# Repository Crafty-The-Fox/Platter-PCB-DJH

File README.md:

# Custom drop-in replacement for the DJ Hero plater PCB with Kailh Choc Mini Switch

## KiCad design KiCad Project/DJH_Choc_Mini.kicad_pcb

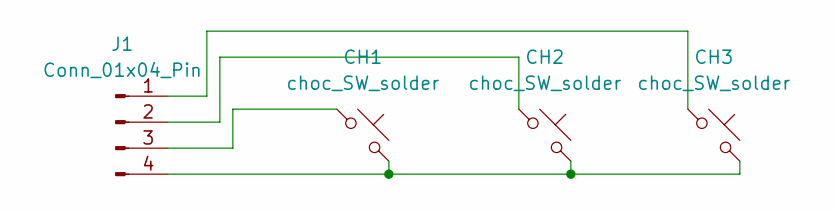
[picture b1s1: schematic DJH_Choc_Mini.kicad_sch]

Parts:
CH1, CH2, CH3: choc_SW_solder; SW_Kailh_Choc_Mini
J1: Conn_01x04_Pin; PinSocket_1x04_P2.54mm_Vertical

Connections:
unnamed: CH3.1, J1.1
unnamed: CH2.1, J1.2
unnamed: CH1.1, J1.3
unnamed: CH1.2, CH2.2, CH3.2, J1.4

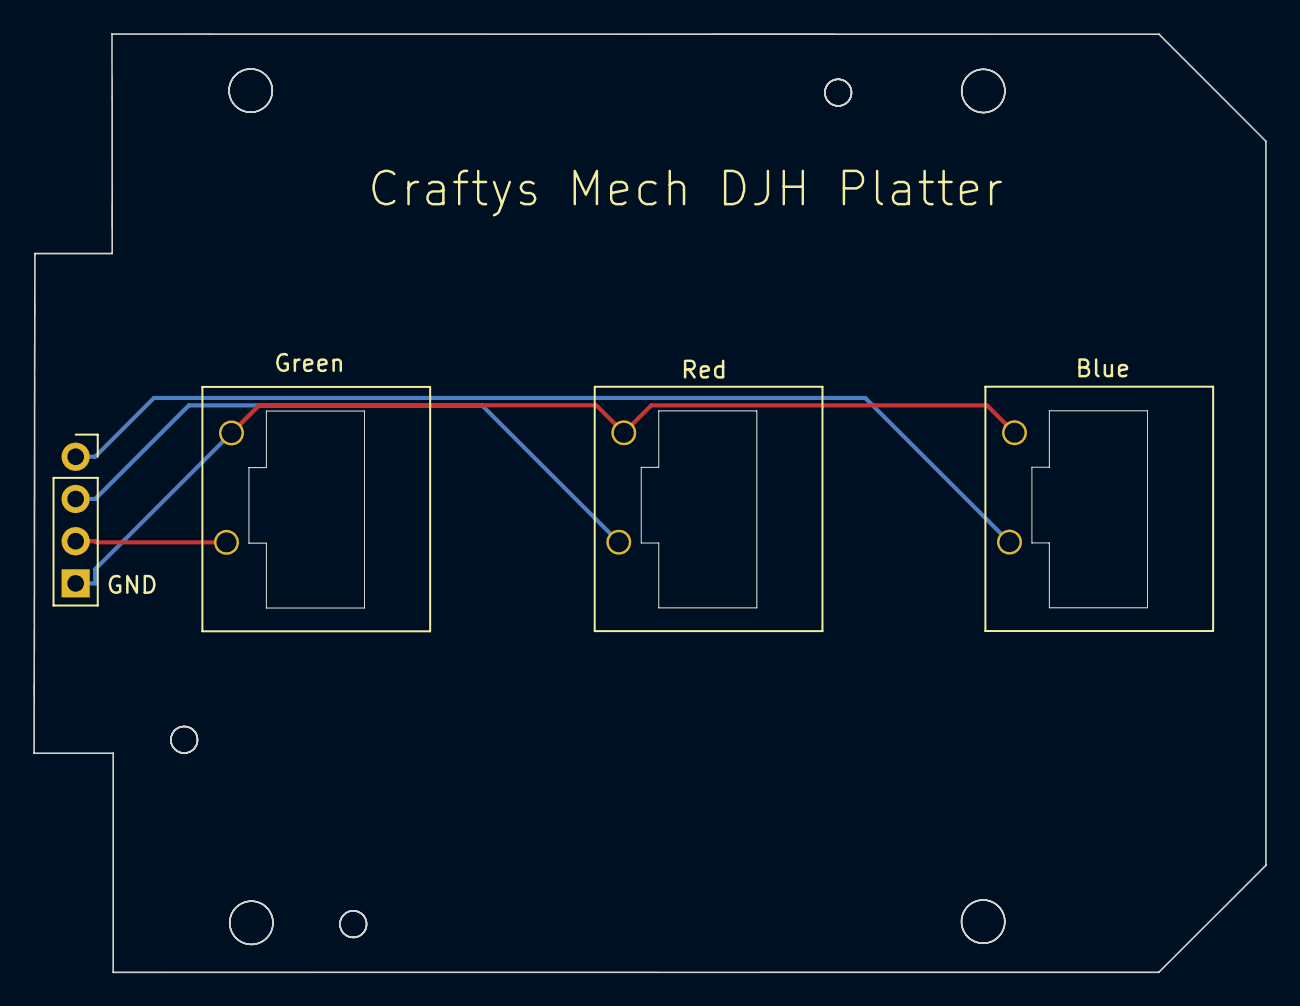
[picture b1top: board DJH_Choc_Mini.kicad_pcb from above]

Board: 2 copper layers, 74.1 x 56.4 mm, 4 parts (0 on the bottom side), 4 nets.

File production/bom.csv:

Designator,Footprint,Quantity,Value,LCSC Part #
"CH1, CH2, CH3",SW_Kailh_Choc_Mini,3,choc_SW_solder,
J1,PinSocket_1x04_P2.54mm_Vertical,1,Conn_01x04_Pin,

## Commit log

2023-08-19 SVG custom PCB template by MAXANGE2B
2023-08-19 Add a PCB Preview PNG
2023-08-19 Add production gerber files
2023-08-19 Add KiCAD Project!
